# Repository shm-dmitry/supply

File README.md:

Supply for my purposes

Yes, I know about china and ali.

But it was intresting to create it manually.

Input: AC 180..240V

Outputs:
1. DC 0..50V up to 10A (banana jack). Support CV and CC modes.
2. DC 5V up to 15A (banana jack & 2.54 pin pannel)
3. DC 3.3V up to 1A
4. one PWM channel 5V & 3.3V up to 1A each (configured from UI)
5. one USB port with QC2.0 chip (up to 18W)
6. two USB ports with 5V/1.5A output
7. One Li-Ion charger with 1A output current

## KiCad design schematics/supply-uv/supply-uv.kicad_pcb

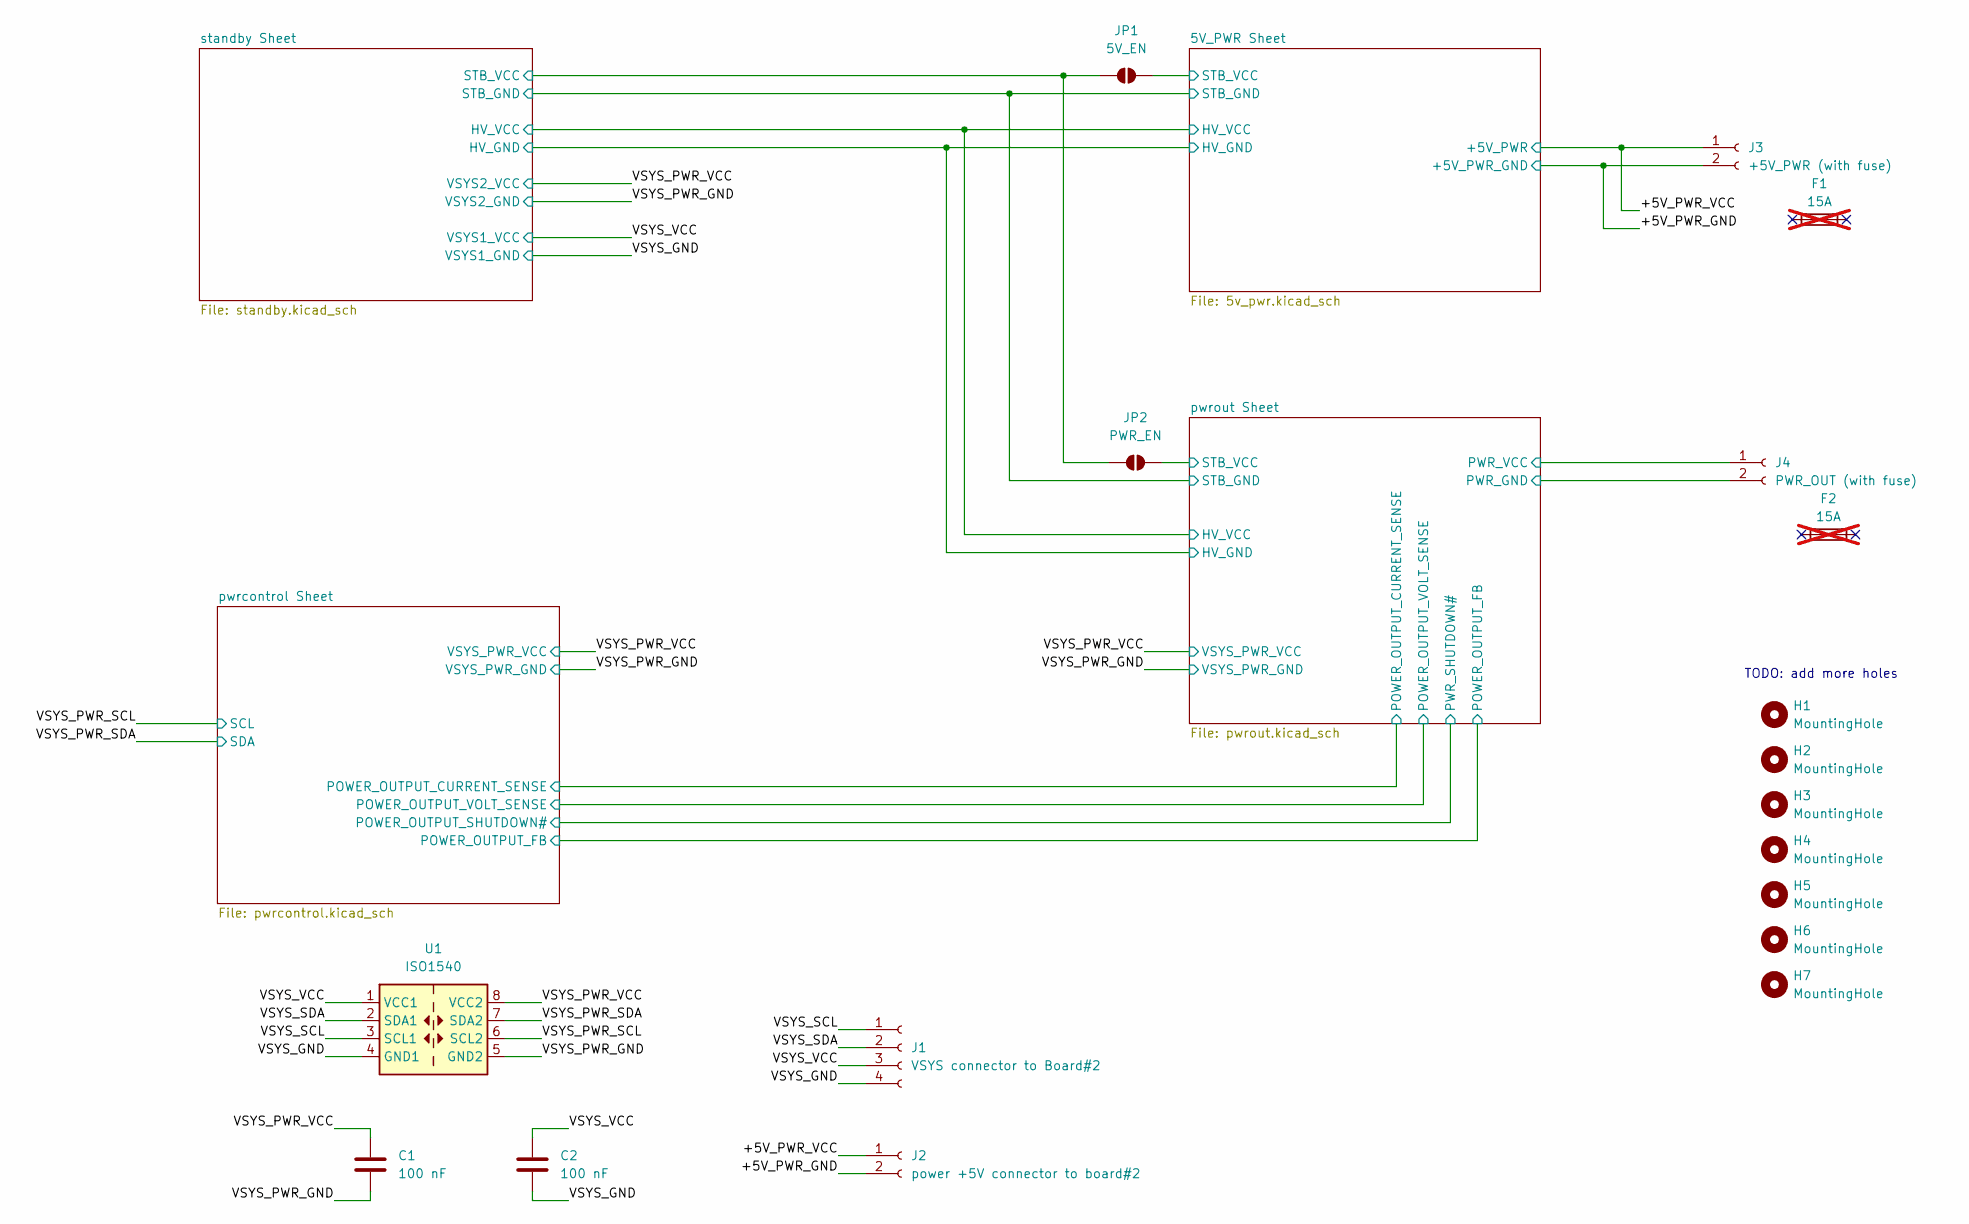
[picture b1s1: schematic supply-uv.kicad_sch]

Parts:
C1, C2: 100 nF; C_0603_1608Metric
F1, F2: 15A; not fitted
H1, H2, H3, H4, H5, H6, H7: MountingHole; MountingHole_2.2mm_M2
J1: VSYS connector to Board#2; JST_XH_B4B-XH-A_1x04_P2.50mm_Vertical
J2: power +5V connector to board#2; SolderWire-1.5sqmm_1x02_P6mm_D1.7mm_OD3mm
J3: +5V_PWR (with fuse); SolderWire-1.5sqmm_1x02_P6mm_D1.7mm_OD3mm
J4: PWR_OUT (with fuse); SolderWire-1.5sqmm_1x02_P6mm_D1.7mm_OD3mm
JP1: 5V_EN; SolderJumper-2_P1.3mm_Open_TrianglePad1.0x1.5mm
JP2: PWR_EN; SolderJumper-2_P1.3mm_Open_TrianglePad1.0x1.5mm
U1: ISO1540; SOIC-8_3.9x4.9mm_P1.27mm

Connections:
/5V_PWR Sheet/STB_VCC: JP1.2 (B); also elsewhere on the board
/+5V_PWR_GND: J2.2, J3.2; also elsewhere on the board
/+5V_PWR_VCC: J2.1, J3.1; also elsewhere on the board
/pwrout Sheet/PWR_GND: J4.2; also elsewhere on the board
/pwrout Sheet/PWR_VCC: J4.1; also elsewhere on the board
/pwrout Sheet/STB_VCC: JP2.2 (B); also elsewhere on the board
/standby Sheet/STB_VCC: JP1.1 (A), JP2.1 (A); also elsewhere on the board

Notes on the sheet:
TODO: add more holes

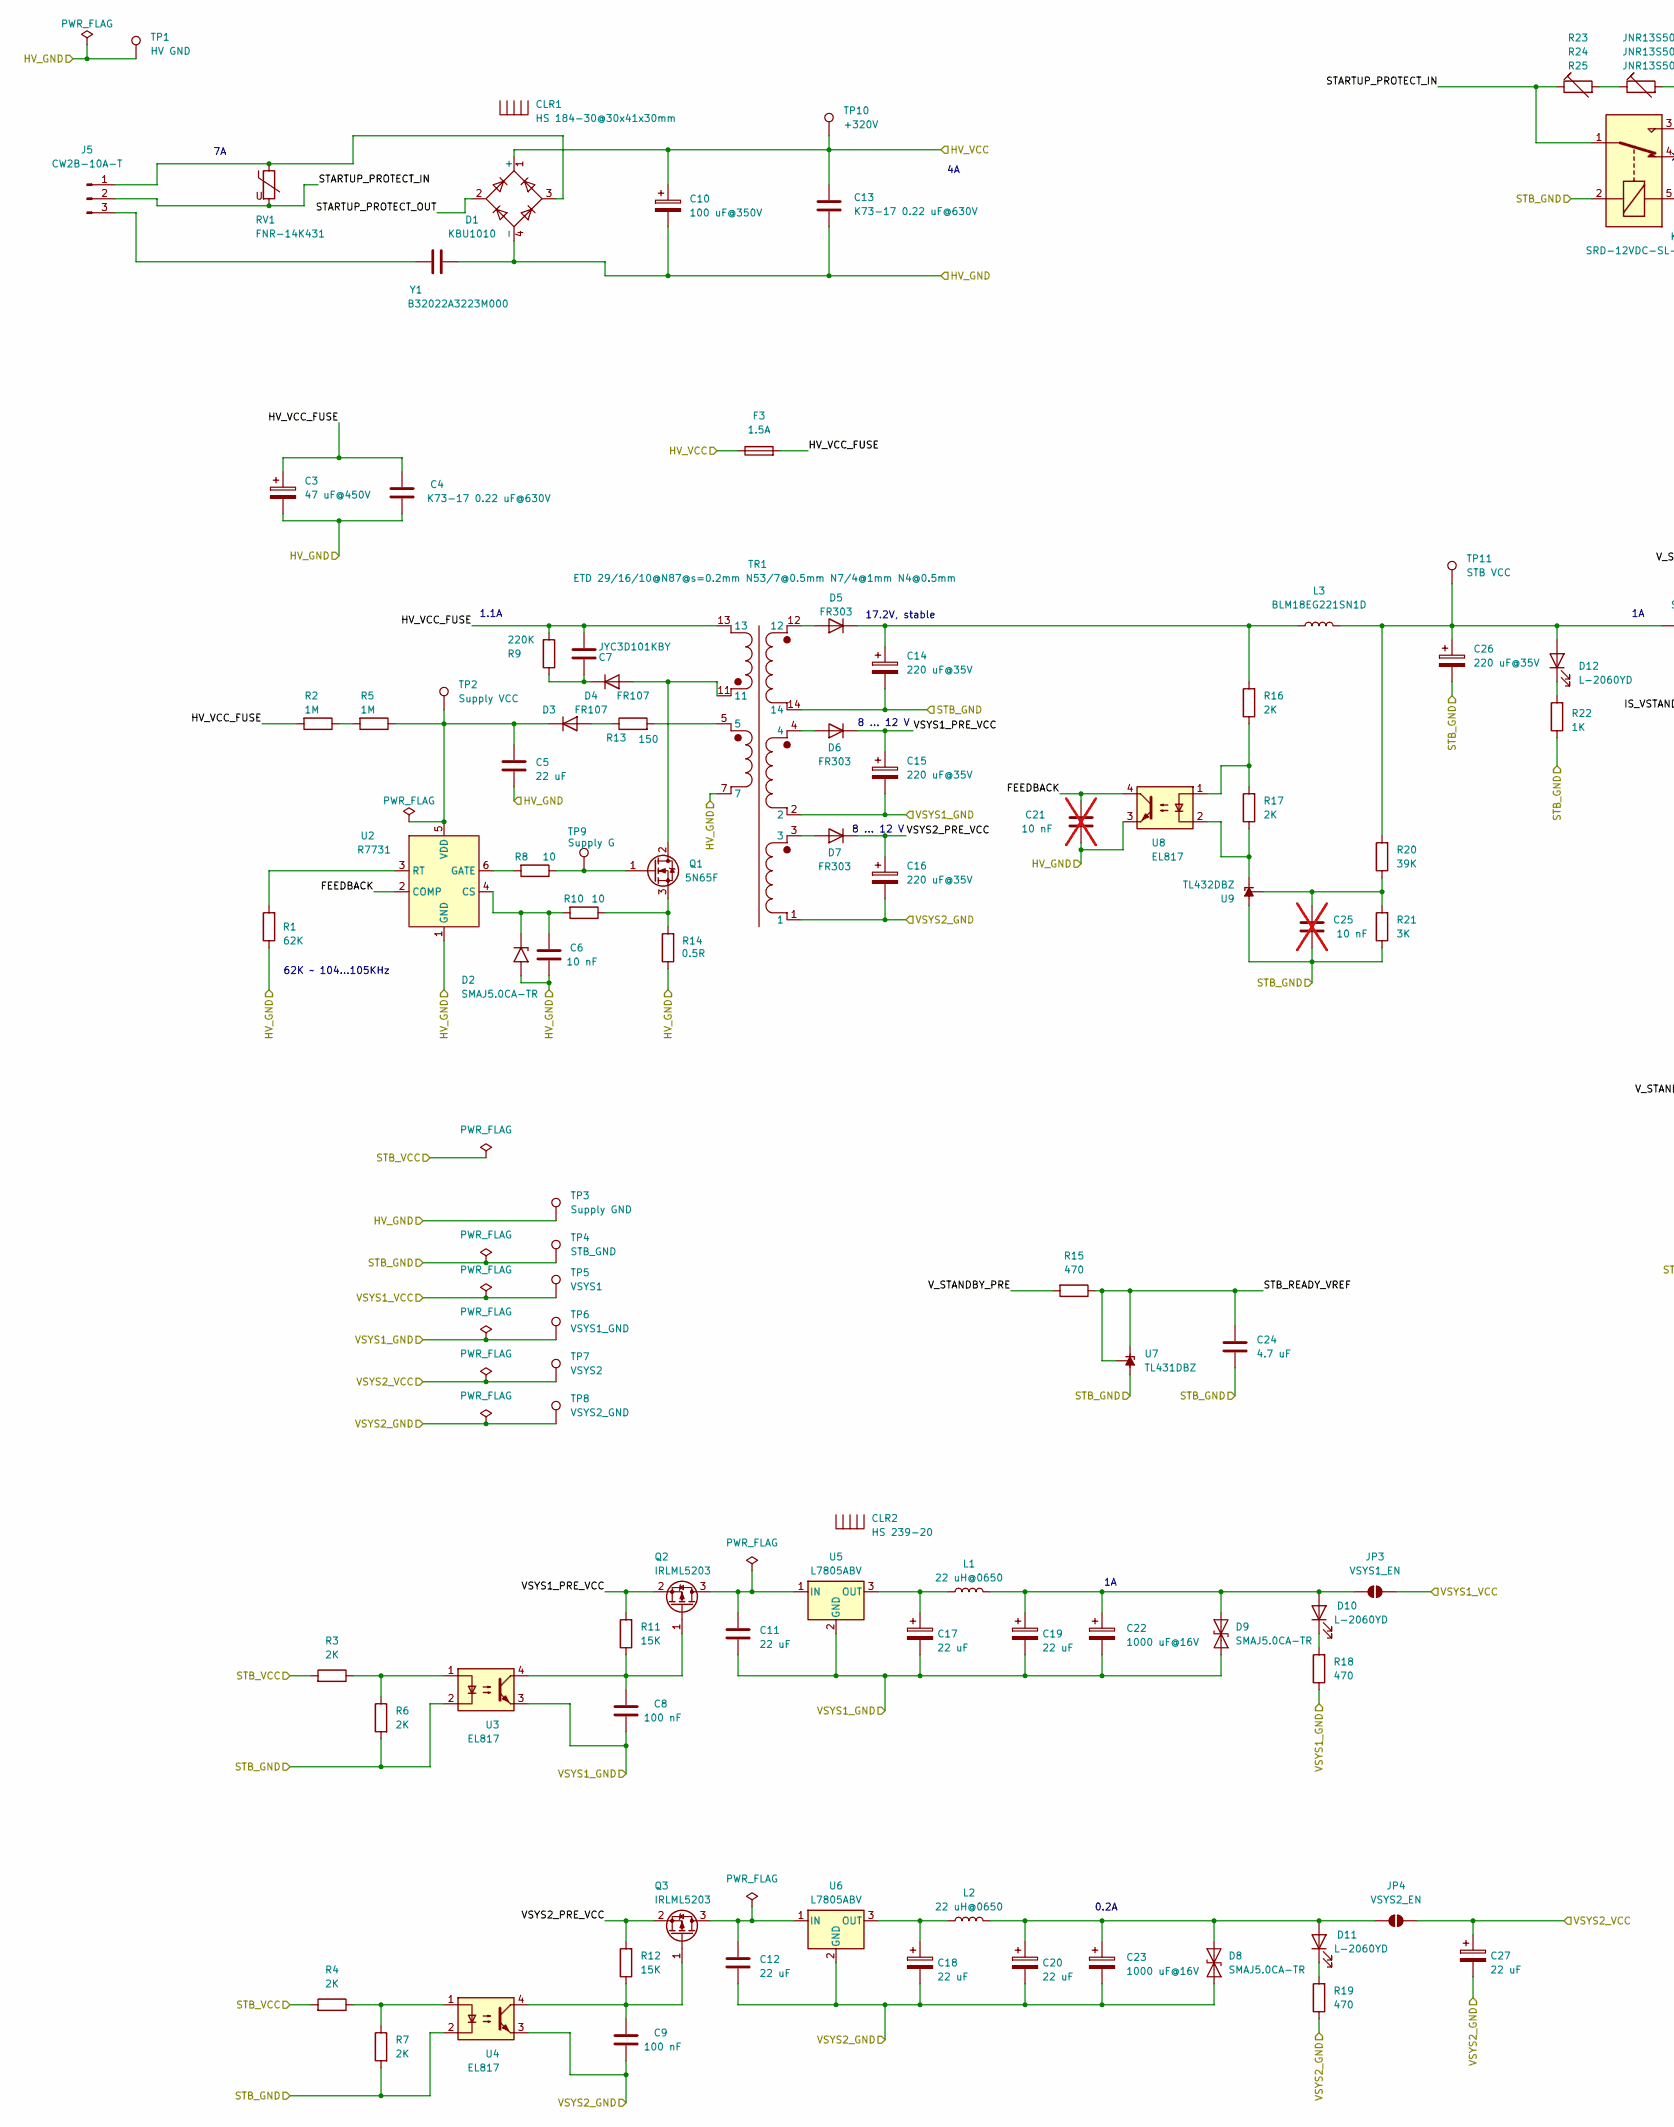
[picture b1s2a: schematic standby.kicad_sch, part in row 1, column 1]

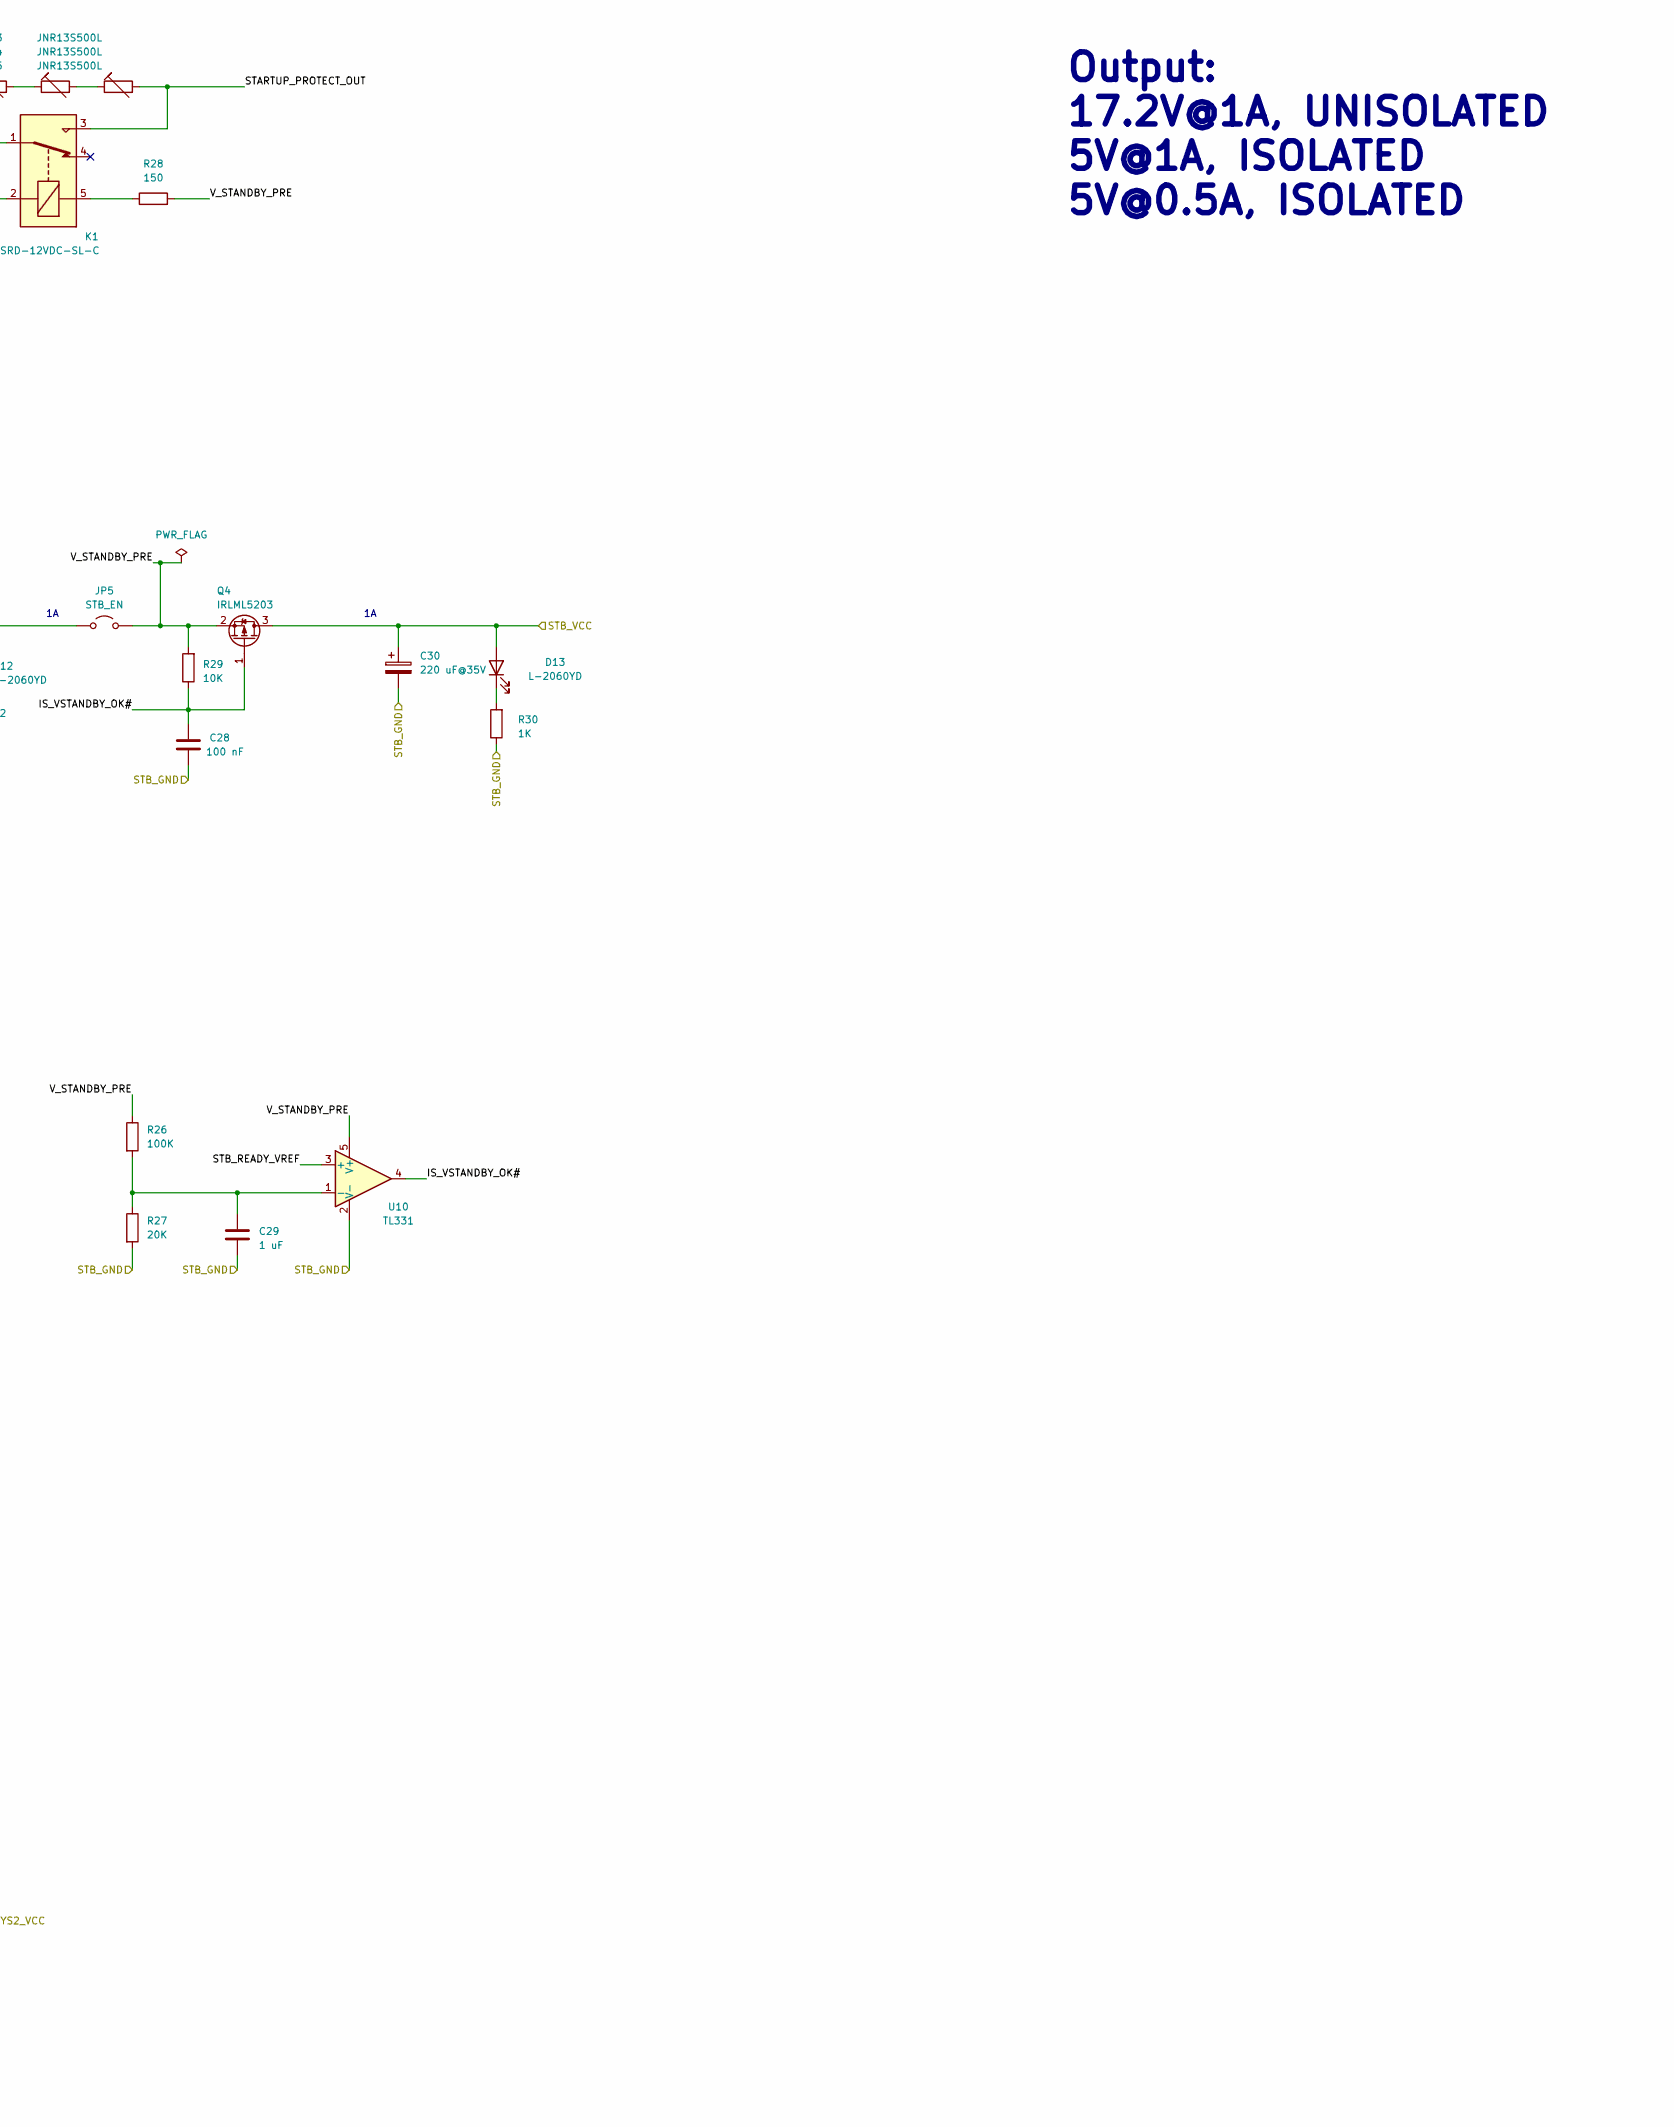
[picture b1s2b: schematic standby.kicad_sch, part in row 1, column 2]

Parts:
C3: 47 uF@450V; CP_Radial_D16.0mm_P7.50mm
C4, C13: К73-17 0.22 uF@630V; C_Axial_L12.0mm_D6.5mm_P20.00mm_Horizontal
C5, C11, C12: 22 uF; C_1210_3225Metric
C6: 10 nF; C_0603_1608Metric
C7: JYC3D101KBY; C_Disc_D7.0mm_W2.5mm_P5.00mm
C8, C9, C28: 100 nF; C_0603_1608Metric
C10: 100 uF@350V; CP_Radial_D18.0mm_P7.50mm
C14, C15, C16, C26, C30: 220 uF@35V; CP_Radial_D8.0mm_P3.50mm
C17, C18, C19, C20, C27: 22 uF; CP_EIA-3216-10_Kemet-I_Pad1.58x1.35mm_HandSolder
C21, C25: 10 nF; C_0603_1608Metric; not fitted
C22, C23: 1000 uF@16V; CP_Radial_D10.0mm_P5.00mm
C24: 4.7 uF; C_0603_1608Metric
C29: 1 uF; C_0603_1608Metric
CLR1: HS 184-30@30х41х30mm; HS-184-30
CLR2: HS 239-20; HS-239-20
D1: KBU1010; Diode_Bridge_Vishay_KBU
D2: SMAJ5.0CA-TR; D_SMB
D3, D4: FR107; D_DO-41_SOD81_P7.62mm_Horizontal
D5, D6, D7: FR303; D_DO-201AD_P3.81mm_Vertical_AnodeUp
D8, D9: SMAJ5.0CA-TR; D_SMA
D10, D11, D12, D13: L-2060YD; LED_D1.8mm_W3.3mm_H2.4mm
F3: 1.5A; FuseHolder1808
J5: CW2B-10A-T; SolderWire-1.5sqmm_1x03_P7.8mm_D1.7mm_OD3.9mm
JP3: VSYS1_EN; SolderJumper-2_P1.3mm_Open_TrianglePad1.0x1.5mm
JP4: VSYS2_EN; SolderJumper-2_P1.3mm_Open_TrianglePad1.0x1.5mm
JP5: STB_EN; TestPoint_2Pads_Pitch2.54mm_Drill0.8mm
K1: SRD-12VDC-SL-C; Relay_SPDT_SANYOU_SRD_Series_Form_C
L1, L2: 22 uH@0650; L_Chilisin_BMRB00060650
L3: BLM18EG221SN1D; L_0603_1608Metric
Q1: 5N65F; TO-220-3_Vertical
Q2, Q3, Q4: IRLML5203; SOT-23
R1: 62K; R_0805_2012Metric
R2, R5: 1M; R_Axial_DIN0207_L6.3mm_D2.5mm_P7.62mm_Horizontal
R3, R4, R6, R7, R16, R17: 2K; R_0805_2012Metric
R8, R10: 10; R_0805_2012Metric
R9: 220K; R_Axial_DIN0207_L6.3mm_D2.5mm_P7.62mm_Horizontal
R11, R12: 15K; R_0805_2012Metric
R13, R28: 150; R_0805_2012Metric
R14: 0.5R; R_2512_6332Metric
R15, R18, R19: 470; R_0805_2012Metric
R20: 39K; R_0805_2012Metric
R21: 3K; R_0805_2012Metric
R22, R30: 1K; R_0805_2012Metric
R23, R24, R25: JNR13S500L; RV_Disc_D12mm_W5.8mm_P7.5mm
R26: 100K; R_0805_2012Metric
R27: 20K; R_0805_2012Metric
R29: 10K; R_0805_2012Metric
RV1: FNR-14K431; R_Radial_Power_L16.1mm_W9.0mm_P7.37mm
TP1: HV GND; TestPoint_Plated_Hole_D1.0mm
TP2: Supply VCC; TestPoint_Pad_1.0x1.0mm
TP3: Supply GND; TestPoint_Plated_Hole_D1.0mm
TP4: STB_GND; TestPoint_Plated_Hole_D1.0mm
TP5: VSYS1; TestPoint_Pad_1.0x1.0mm
TP6: VSYS1_GND; TestPoint_Plated_Hole_D1.0mm
TP7: VSYS2; TestPoint_Pad_1.0x1.0mm
TP8: VSYS2_GND; TestPoint_Plated_Hole_D1.0mm
TP9: Supply G; TestPoint_Pad_1.0x1.0mm
TP10: +320V; TestPoint_Pad_1.0x1.0mm
TP11: STB VCC; TestPoint_Pad_1.0x1.0mm
TR1: ETD 29/16/10@N87@s=0.2mm N53/7@0.5mm N7/4@1mm N4@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; ETD29_7x7_vertical
U2: R7731; SOT-23-6
U3, U4, U8: EL817; DIP-4_W7.62mm
U5, U6: L7805ABV; TO-220-3_Vertical
U7: TL431DBZ; SOT-23
U9: TL432DBZ; SOT-23-3
U10: TL331; SOT-23-5
Y1: B32022A3223M000; C_Rect_L18.0mm_W6.0mm_P15.00mm_FKS3_FKP3

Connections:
/5V_PWR Sheet/HV_GND: C3.2, C4.1, C5.1, C6.1, C10.2, C13.1, C21.1, D1.4 (-), D2.2 (A2), R1.1, R14.1, TP1.1, TP3.1, TR1.7, U2.1 (GND), U8.3, Y1.2; also elsewhere on the board
/5V_PWR Sheet/HV_VCC: C10.1, C13.2, D1.1 (+), F3.1, TP10.1; also elsewhere on the board
/5V_PWR Sheet/STB_GND: C14.2, C24.2, C25.1, C26.2, C28.1, C29.2, C30.2, K1.2, R6.2, R7.2, R21.1, R22.1, R27.2, R30.1, TP4.1, TR1.14, U3.2, U4.2, U7.3 (A), U9.3 (A), U10.2 (V-); also elsewhere on the board
/standby Sheet/FEEDBACK: C21.2, U2.2 (COMP), U8.4
/standby Sheet/HV_VCC_FUSE: C3.1, C4.2, C7.2, F3.2, R2.2, R9.2, TR1.13
/standby Sheet/IS_VSTANDBY_OK#: C28.2, Q4.1 (G), R29.1, U10.4
/standby Sheet/STARTUP_PROTECT_IN: J5.2, K1.1, R23.1, RV1.2
/standby Sheet/STARTUP_PROTECT_OUT: D1.2, K1.3, R25.2
/standby Sheet/STB_READY_VREF: C24.1, R15.1, U7.1 (K), U7.2 (REF), U10.3 (+)
/standby Sheet/STB_VCC: C30.1, D13.2 (A), Q4.3 (D), R3.2, R4.2; also elsewhere on the board
/standby Sheet/VSYS1_PRE_VCC: C15.1, D6.1 (K), Q2.2 (S), R11.2
/standby Sheet/VSYS2_PRE_VCC: C16.1, D7.1 (K), Q3.2 (S), R12.2
/standby Sheet/V_STANDBY_PRE: JP5.2 (B), Q4.2 (S), R15.2, R26.1, R28.2, R29.2, U10.5 (V+)
unnamed: C6.2, D2.1 (A1), R10.2, U2.4 (CS)
unnamed: D3.2 (A), R13.1
unnamed: C5.2, D3.1 (K), R5.1, TP2.1, U2.5 (VDD)
unnamed: D4.2 (A), Q1.2 (D), TR1.11
unnamed: C7.1, D4.1 (K), R9.1
unnamed: D5.2 (A), TR1.12
unnamed: C14.1, D5.1 (K), L3.1, R16.2
unnamed: D6.2 (A), TR1.4
unnamed: D7.2 (A), TR1.3
unnamed: C19.1, C22.1, D9.2 (A2), D10.2 (A), JP3.1 (A), L1.2
unnamed: D10.1 (K), R18.2
unnamed: C20.1, C23.1, D8.2 (A2), D11.2 (A), JP4.1 (A), L2.2
unnamed: D11.1 (K), R19.2
unnamed: C26.1, D12.2 (A), JP5.1 (A), L3.2, R20.2, TP11.1
unnamed: D12.1 (K), R22.2
unnamed: D13.1 (K), R30.2
unnamed: D1.3, J5.1, RV1.1
unnamed: J5.3, Y1.1
unnamed: K1.5, R28.1
unnamed: Q1.1 (G), R8.1, TP9.1
unnamed: Q1.3 (S), R10.1, R14.2
unnamed: C11.2, Q2.3 (D), U5.1 (IN)
unnamed: C8.2, Q2.1 (G), R11.1, U3.4
unnamed: C12.2, Q3.3 (D), U6.1 (IN)
unnamed: C9.2, Q3.1 (G), R12.1, U4.4
unnamed: R2.1, R5.2
unnamed: R3.1, R6.1, U3.1
unnamed: R4.1, R7.1, U4.1
unnamed: R13.2, TR1.5
unnamed: R16.1, R17.2, U8.1
unnamed: R23.2, R24.1
unnamed: R24.2, R25.1
unnamed: R8.2, U2.6 (GATE)
unnamed: R1.2, U2.3 (RT)
unnamed: C17.1, L1.1, U5.3 (OUT)
unnamed: C18.1, L2.1, U6.3 (OUT)
unnamed: R17.1, U8.2, U9.2 (K)
unnamed: C25.2, R20.1, R21.2, U9.1 (REF)
unnamed: C29.1, R26.2, R27.1, U10.1 (-)

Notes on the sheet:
8 ... 12 V
1.1A
17.2V, stable
Output: 17.2V@1A, UNISOLATED 5V@1A, ISOLATED 5V@0.5A, ISOLATED
62K ~ 104...105KHz
0.2A

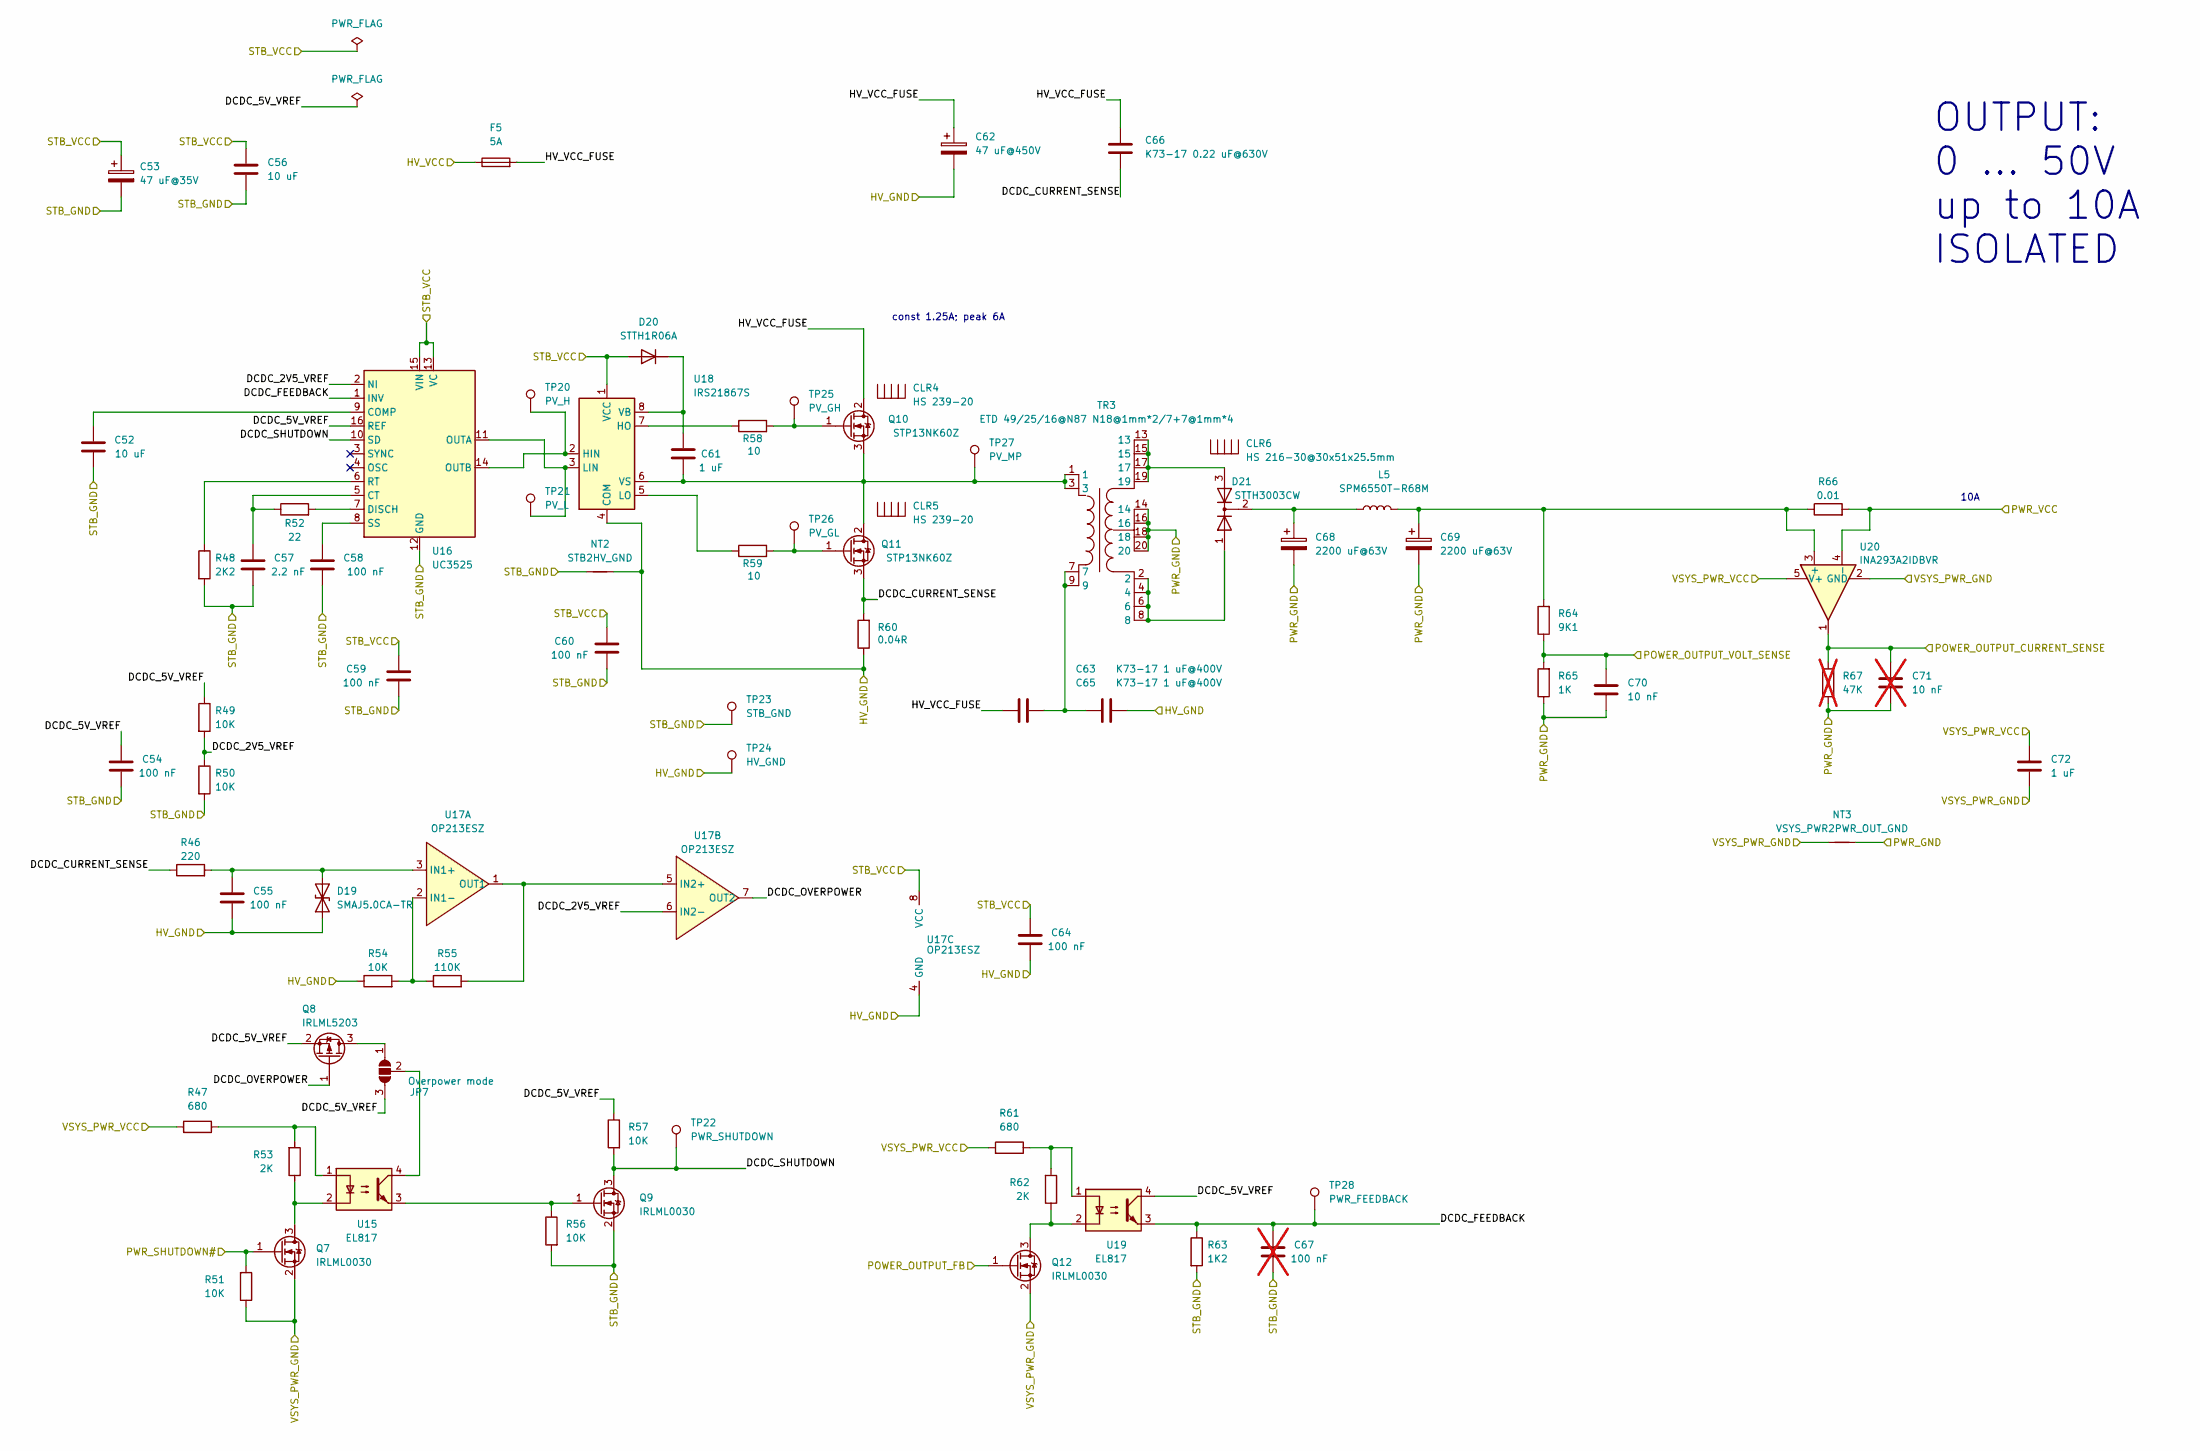
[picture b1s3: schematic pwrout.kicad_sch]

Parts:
C52, C56: 10 uF; C_0603_1608Metric
C53: 47 uF@35V; CP_Radial_D6.3mm_P2.50mm
C54, C55, C58, C59, C60, C64: 100 nF; C_0603_1608Metric
C57: 2.2 nF; C_0603_1608Metric
C61, C72: 1 uF; C_0603_1608Metric
C62: 47 uF@450V; CP_Radial_D16.0mm_P7.50mm
C63, C65: К73-17 1 uF@400V; C_Rect_L24.0mm_W12.8mm_P22.50mm_MKT
C66: К73-17 0.22 uF@630V; C_Axial_L12.0mm_D6.5mm_P20.00mm_Horizontal
C67: 100 nF; C_0603_1608Metric; not fitted
C68, C69: 2200 uF@63V; CP_Radial_D18.0mm_P7.50mm
C70: 10 nF; C_0603_1608Metric
C71: 10 nF; C_0603_1608Metric; not fitted
CLR4, CLR5: HS 239-20; HS-239-20
CLR6: HS 216-30@30х51х25.5mm; HS 216-30
D19: SMAJ5.0CA-TR; D_SMB
D20: STTH1R06A; D_SMA
D21: STTH3003CW; TO-247-3_Vertical
F5: 5A; FuseHolder1808
JP7: Overpower mode; SolderJumper-3_P1.3mm_Bridged2Bar12_RoundedPad1.0x1.5mm_Num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
L5: SPM6550T-R68M; L_Sumida_CDMC6D28_7.25x6.5mm
NT2: STB2HV_GND; NetTie-2_SMD_Pad0.5mm
NT3: VSYS_PWR2PWR_OUT_GND; NetTie-2_SMD_Pad0.5mm
Q7, Q9, Q12: IRLML0030; SOT-23
Q8: IRLML5203; SOT-23
Q10, Q11: STP13NK60Z; TO-220-3_Vertical
R46: 220; R_0805_2012Metric
R47, R61: 680; R_0805_2012Metric
R48: 2K2; R_0805_2012Metric
R49, R50, R51, R54, R56, R57: 10K; R_0805_2012Metric
R52: 22; R_0805_2012Metric
R53, R62: 2K; R_0805_2012Metric
R55: 110K; R_0805_2012Metric
R58, R59: 10; R_0805_2012Metric
R60: 0.04R; R_2512_6332Metric
R63: 1K2; R_0805_2012Metric
R64: 9K1; R_0805_2012Metric
R65: 1K; R_0805_2012Metric
R66: 0.01; R_2512_6332Metric
R67: 47K; R_0805_2012Metric; not fitted
TP20: PV_H; TestPoint_Pad_1.0x1.0mm
TP21: PV_L; TestPoint_Pad_1.0x1.0mm
TP22: PWR_SHUTDOWN; TestPoint_Pad_1.0x1.0mm
TP23: STB_GND; TestPoint_Plated_Hole_D1.0mm
TP24: HV_GND; TestPoint_Plated_Hole_D1.0mm
TP25: PV_GH; TestPoint_Pad_1.0x1.0mm
TP26: PV_GL; TestPoint_Pad_1.0x1.0mm
TP27: PV_MP; TestPoint_Pad_1.0x1.0mm
TP28: PWR_FEEDBACK; TestPoint_Pad_1.0x1.0mm
TR3: ETD 49/25/16@N87 N18@1mm*2/7+7@1mm*4; ETD49_10x10_horizontal
U15, U19: EL817; DIP-4_W7.62mm
U16: UC3525; SOIC-16W_7.5x10.3mm_P1.27mm
U17: OP213ESZ; SO-8_3.9x4.9mm_P1.27mm
U18: IRS21867S; SOIC-8_3.9x4.9mm_P1.27mm
U20: INA293A2IDBVR; SOT-23-5

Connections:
/5V_PWR Sheet/HV_GND: C55.2, C62.2, C64.2, C65.1, D19.1 (A1), NT2.2, R54.1, R60.1, TP24.1, U17.4 (GND), U18.4 (COM); also elsewhere on the board
/5V_PWR Sheet/HV_VCC: F5.1; also elsewhere on the board
/5V_PWR Sheet/STB_GND: C52.2, C53.2, C54.2, C56.1, C57.2, C58.2, C59.2, C60.2, C67.2, NT2.1, Q9.2 (S), R48.2, R50.2, R56.2, R63.2, TP23.1, U16.12 (GND); also elsewhere on the board
/pwrcontrol Sheet/POWER_OUTPUT_CURRENT_SENSE: C71.2, R67.2, U20.1; also elsewhere on the board
/pwrcontrol Sheet/POWER_OUTPUT_FB: Q12.1 (G); also elsewhere on the board
/pwrcontrol Sheet/POWER_OUTPUT_SHUTDOWN#: Q7.1 (G), R51.2; also elsewhere on the board
/pwrcontrol Sheet/POWER_OUTPUT_VOLT_SENSE: C70.2, R64.1, R65.2; also elsewhere on the board
/pwrout Sheet/DCDC_2V5_VREF: R49.2, R50.1, U16.2 (NI), U17.6 (IN2-)
/pwrout Sheet/DCDC_5V_VREF: C54.1, JP7.3 (B), Q8.2 (S), R49.1, R57.1, U16.16 (REF), U19.4
/pwrout Sheet/DCDC_CURRENT_SENSE: C66.1, Q11.3 (S), R46.1, R60.2
/pwrout Sheet/DCDC_FEEDBACK: C67.1, R63.1, TP28.1, U16.1 (INV), U19.3
/pwrout Sheet/DCDC_OVERPOWER#: Q8.1 (G), U17.7 (OUT2)
/pwrout Sheet/DCDC_SHUTDOWN: Q9.3 (D), R57.2, TP22.1, U16.10 (SD)
/pwrout Sheet/HV_VCC_FUSE: C62.1, C63.2, C66.2, F5.2, Q10.2 (D)
/pwrout Sheet/PWR_GND: C68.2, C69.2, C70.1, C71.1, NT3.2, R65.1, R67.1, TR3.14, TR3.16, TR3.18, TR3.20; also elsewhere on the board
/pwrout Sheet/PWR_VCC: R66.2, U20.4 (-); also elsewhere on the board
/pwrout Sheet/STB_VCC: C53.1, C56.2, C59.1, C60.1, C64.1, D20.2 (A), U16.13 (VC), U16.15 (VIN), U17.8 (VCC), U18.1 (VCC); also elsewhere on the board
unnamed: C63.1, C65.2, TR3.7, TR3.9
unnamed: C55.1, D19.2 (A2), R46.2, U17.3 (IN1+)
unnamed: C61.1, D20.1 (K), U18.8 (VB)
unnamed: D21.1 (A), TR3.2, TR3.4, TR3.6, TR3.8
unnamed: D21.3 (A), TR3.13, TR3.15, TR3.17, TR3.19
unnamed: C68.1, D21.2 (K), L5.1
unnamed: JP7.1 (A), Q8.3 (D)
unnamed: JP7.2 (C), U15.4
unnamed: Q7.3 (D), R53.1, U15.2
unnamed: Q9.1 (G), R56.1, U15.3
unnamed: Q10.1 (G), R58.2, TP25.1
unnamed: C61.2, Q10.3 (S), Q11.2 (D), TP27.1, TR3.1, TR3.3, U18.6 (VS)
unnamed: Q11.1 (G), R59.2, TP26.1
unnamed: Q12.3 (D), R62.1, U19.2
unnamed: R47.1, R53.2, U15.1
unnamed: R61.1, R62.2, U19.1
unnamed: C52.1, U16.9 (COMP)
unnamed: C57.1, R52.1, U16.5 (CT)
unnamed: R52.2, U16.7 (DISCH)
unnamed: TP21.1, U16.11 (OUTA), U18.3 (LIN)
unnamed: TP20.1, U16.14 (OUTB), U18.2 (HIN)
unnamed: R48.1, U16.6 (RT)
unnamed: C58.1, U16.8 (SS)
unnamed: R54.2, R55.1, U17.2 (IN1-)
unnamed: R55.2, U17.1 (OUT1), U17.5 (IN2+)
unnamed: R58.1, U18.7 (HO)
unnamed: R59.1, U18.5 (LO)
unnamed: C69.1, L5.2, R64.2, R66.1, U20.3 (+)

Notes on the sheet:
OUTPUT: 0 ... 50V up to 10A ISOLATED
10A
const 1.25A; peak 6A

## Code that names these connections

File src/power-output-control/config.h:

#ifndef CONFIG_H_
#define CONFIG_H_

#define UART_ENABLED true
#define SET_DEFAULT_V_I_ON_START false

// C2
#define PIN_LED_OVERLOADED 12
// C3
#define PIN_LED_POWEROUTPUT 13

// A7
#define PIN_POWER_OUTPUT_SENSE_I PIN_PA7
// B4
#define PIN_POWER_OUTPUT_SENSE_V PIN_PB4
// A6
#define PIN_POWER_OUTPUT_VREF    PIN_PA6

// A5
#define PIN_POWER_OUTPUT_IC_FB A5
// B5
#define PIN_POWER_OUTPUT_SHUTDOWN PIN_PB5

#define I2C_SLAVE_ADDRESS 0x33

#endif /* #define CONFIG_H_ */

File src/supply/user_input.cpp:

#include "user_input.h"

#include "Arduino.h"

#include "config.h"

#define USERINPUT_BIT_I_LEFT     (_BV(0))
#define USERINPUT_BIT_I_RIGHT    (_BV(1))
#define USERINPUT_BIT_I_CLICK    (_BV(2))
#define USERINPUT_BIT_I_FAST     (_BV(3))

#define USERINPUT_BIT_V_LEFT     (_BV(4))
#define USERINPUT_BIT_V_RIGHT    (_BV(5))
#define USERINPUT_BIT_V_CLICK    (_BV(6))
#define USERINPUT_BIT_V_FAST     (_BV(7))

#define USERINPUT_PIN_I_A       PD2
#define USERINPUT_PIN_I_B       PD3
#define USERINPUT_PIN_I_CLICK   PD4
#define USERINPUT_PIN_V_A       PD5
#define USERINPUT_PIN_V_B       PD6
#define USERINPUT_PIN_V_CLICK   PD7
#define USERINPUT_PIN_ONOFF     8

#define USERINPUT_ONOFF_AWAIT_NEXT_PRESS 100

volatile uint8_t user_input_flags = 0;
volatile uint32_t user_input_onoff_next_press = 0;
volatile bool user_input_onoff_await_release = false;

volatile uint8_t userinput_i_lastStateA = LOW;
volatile bool userinput_i_turnFlag = false;

volatile uint8_t userinput_v_lastStateA = LOW;
volatile bool userinput_v_turnFlag = false;

#define USERINPUT_SETFLAG(flag)   user_input_flags |= flag
#define USERINPUT_RESETFLAG(flag) user_input_flags &= ~(flag)

void isrcall_process_encoder(bool first);

ISR(PCINT2_vect) {
  if (digitalRead(USERINPUT_PIN_I_CLICK) == LOW) {
    USERINPUT_SETFLAG(USERINPUT_BIT_I_CLICK);
  }

  if (digitalRead(USERINPUT_PIN_V_CLICK) == LOW) {
    USERINPUT_SETFLAG(USERINPUT_BIT_V_CLICK);
  }

  #if USER_INPUT_SIMUL
  if (digitalRead(USERINPUT_PIN_I_A) == LOW) {
    USERINPUT_SETFLAG(USERINPUT_BIT_I_LEFT);
  } else if (digitalRead(USERINPUT_PIN_I_B) == LOW) {
    USERINPUT_SETFLAG(USERINPUT_BIT_I_RIGHT);
  }

  if (digitalRead(USERINPUT_PIN_V_A) == LOW) {
    USERINPUT_SETFLAG(USERINPUT_BIT_V_LEFT);
  } else if (digitalRead(USERINPUT_PIN_V_B) == LOW) {
    USERINPUT_SETFLAG(USERINPUT_BIT_V_RIGHT);
  }
  #else
  
  uint8_t stateiA = digitalRead(USERINPUT_PIN_I_A);
  uint8_t statevA = digitalRead(USERINPUT_PIN_V_A);

  if (stateiA != userinput_i_lastStateA) {
    userinput_i_lastStateA = stateiA;
    userinput_i_turnFlag   = !userinput_i_turnFlag;
    if (userinput_i_turnFlag) {
      if (digitalRead(USERINPUT_PIN_I_B) != stateiA) {
        if (user_input_flags & USERINPUT_BIT_I_LEFT) {
          USERINPUT_SETFLAG(USERINPUT_BIT_I_FAST);
        } else {
          USERINPUT_SETFLAG(USERINPUT_BIT_I_LEFT);
          USERINPUT_RESETFLAG(USERINPUT_BIT_I_RIGHT & USERINPUT_BIT_I_FAST);
        }
      } else {
        if (user_input_flags & USERINPUT_BIT_I_RIGHT) {
          USERINPUT_SETFLAG(USERINPUT_BIT_I_FAST);
        } else {
          USERINPUT_SETFLAG(USERINPUT_BIT_I_RIGHT);
          USERINPUT_RESETFLAG(USERINPUT_BIT_I_LEFT & USERINPUT_BIT_I_FAST);
        }
      }
    }
  }

  if (statevA != userinput_v_lastStateA) {
    userinput_v_lastStateA = statevA;
    userinput_v_turnFlag   = !userinput_v_turnFlag;
    if (userinput_v_turnFlag) {
      if (digitalRead(USERINPUT_PIN_V_B) != statevA) {
        if (user_input_flags & USERINPUT_BIT_V_LEFT) {
          USERINPUT_SETFLAG(USERINPUT_BIT_V_FAST);
        } else {
          USERINPUT_SETFLAG(USERINPUT_BIT_V_LEFT);
          USERINPUT_RESETFLAG(USERINPUT_BIT_V_RIGHT & USERINPUT_BIT_V_FAST);
        }
      } else {
        if (user_input_flags & USERINPUT_BIT_V_RIGHT) {
          USERINPUT_SETFLAG(USERINPUT_BIT_V_FAST);
        } else {
          USERINPUT_SETFLAG(USERINPUT_BIT_V_RIGHT);
          USERINPUT_RESETFLAG(USERINPUT_BIT_V_LEFT & USERINPUT_BIT_V_FAST);
        }
      }
    }
  }

  #endif
}

void user_input_init() {
  pinMode(USERINPUT_PIN_I_A,      INPUT_PULLUP);
  pinMode(USERINPUT_PIN_I_B,      INPUT_PULLUP);
  pinMode(USERINPUT_PIN_I_CLICK,  INPUT_PULLUP);

  pinMode(USERINPUT_PIN_V_A,      INPUT_PULLUP);
  pinMode(USERINPUT_PIN_V_B,      INPUT_PULLUP);
  pinMode(USERINPUT_PIN_V_CLICK,  INPUT_PULLUP);

  pinMode(USERINPUT_PIN_ONOFF, INPUT);

  PCICR = 0;
  PCMSK2 = _BV(PCINT18) | _BV(PCINT19) | _BV(PCINT20) | _BV(PCINT21) | _BV(PCINT22) | _BV(PCINT23);
}

bool user_input_onoff_pressed() {
  if (user_input_onoff_next_press < millis()) {
    if (digitalRead(USERINPUT_PIN_ONOFF) == HIGH) {
      if (!user_input_onoff_await_release) {
        user_input_onoff_await_release = true;
        Serial.println("ON/OFF pressed");
        return true;
      }
    } else {
      if (user_input_onoff_await_release) {
        user_input_onoff_next_press = millis() + USERINPUT_ONOFF_AWAIT_NEXT_PRESS;
        user_input_onoff_await_release = false;
      }
    }
  }

  return false;
}

uint8_t user_input_encoder_i_status() {
  uint8_t result = USER_INPUT_STATUS_NONE;

  uint8_t oldSREG = SREG;
  cli();

  if (user_input_flags & USERINPUT_BIT_I_CLICK) {
    USERINPUT_RESETFLAG(USERINPUT_BIT_I_CLICK);
    result = USER_INPUT_STATUS_CLICK;
  } else if (user_input_flags & USERINPUT_BIT_I_LEFT) {
    if (user_input_flags & USERINPUT_BIT_I_FAST) {
      USERINPUT_RESETFLAG(USERINPUT_BIT_I_FAST);
      result = USER_INPUT_STATUS_LEFT_FAST;
    } else {
      USERINPUT_RESETFLAG(USERINPUT_BIT_I_LEFT);
      result = USER_INPUT_STATUS_LEFT;
    }
  } else if (user_input_flags & USERINPUT_BIT_I_RIGHT) {
    if (user_input_flags & USERINPUT_BIT_I_FAST) {
      USERINPUT_RESETFLAG(USERINPUT_BIT_I_FAST);
      result = USER_INPUT_STATUS_RIGHT_FAST;
    } else {
      USERINPUT_RESETFLAG(USERINPUT_BIT_I_RIGHT);
      result = USER_INPUT_STATUS_RIGHT;
    }
  }

  SREG = oldSREG;

  return result;
}

uint8_t user_input_encoder_v_status() {
  uint8_t result = USER_INPUT_STATUS_NONE;

  uint8_t oldSREG = SREG;
  cli();

  if (user_input_flags & USERINPUT_BIT_V_CLICK) {
    USERINPUT_RESETFLAG(USERINPUT_BIT_V_CLICK);
    result = USER_INPUT_STATUS_CLICK;
  } else if (user_input_flags & USERINPUT_BIT_V_LEFT) {
    if (user_input_flags & USERINPUT_BIT_V_FAST) {
      USERINPUT_RESETFLAG(USERINPUT_BIT_V_FAST);
      result = USER_INPUT_STATUS_LEFT_FAST;
    } else {
      USERINPUT_RESETFLAG(USERINPUT_BIT_V_LEFT);
      result = USER_INPUT_STATUS_LEFT;
    }
  } else if (user_input_flags & USERINPUT_BIT_V_RIGHT) {
    if (user_input_flags & USERINPUT_BIT_V_FAST) {
      USERINPUT_RESETFLAG(USERINPUT_BIT_V_FAST);
      result = USER_INPUT_STATUS_RIGHT_FAST;
    } else {
      USERINPUT_RESETFLAG(USERINPUT_BIT_V_RIGHT);
      result = USER_INPUT_STATUS_RIGHT;
    }
  }

  SREG = oldSREG;
  
  return result;
}

void user_input_start() {
  PCICR =  _BV(PCIE2);
}
